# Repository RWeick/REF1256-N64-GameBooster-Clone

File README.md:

# REF1256-N64-GameBooster-Clone
An open source clone of the Datel GameBooster for the Nintendo 64

This is a fully functional Nintendo 64 GameBooster clone. It implements the original LZ9FC17 GAL on an Altera EPM570, and fully supports all functionality to include: loading Gameboy cartridges and the GS button.

This is compatible with the Sanni Cartridge Reader's N64 Gameshark programming function.

The 2x5 10 pin connector is mapped to the standard Altera USB Blaster pinout for programming. Happy making.

PCB Thickness: 1.2 mm

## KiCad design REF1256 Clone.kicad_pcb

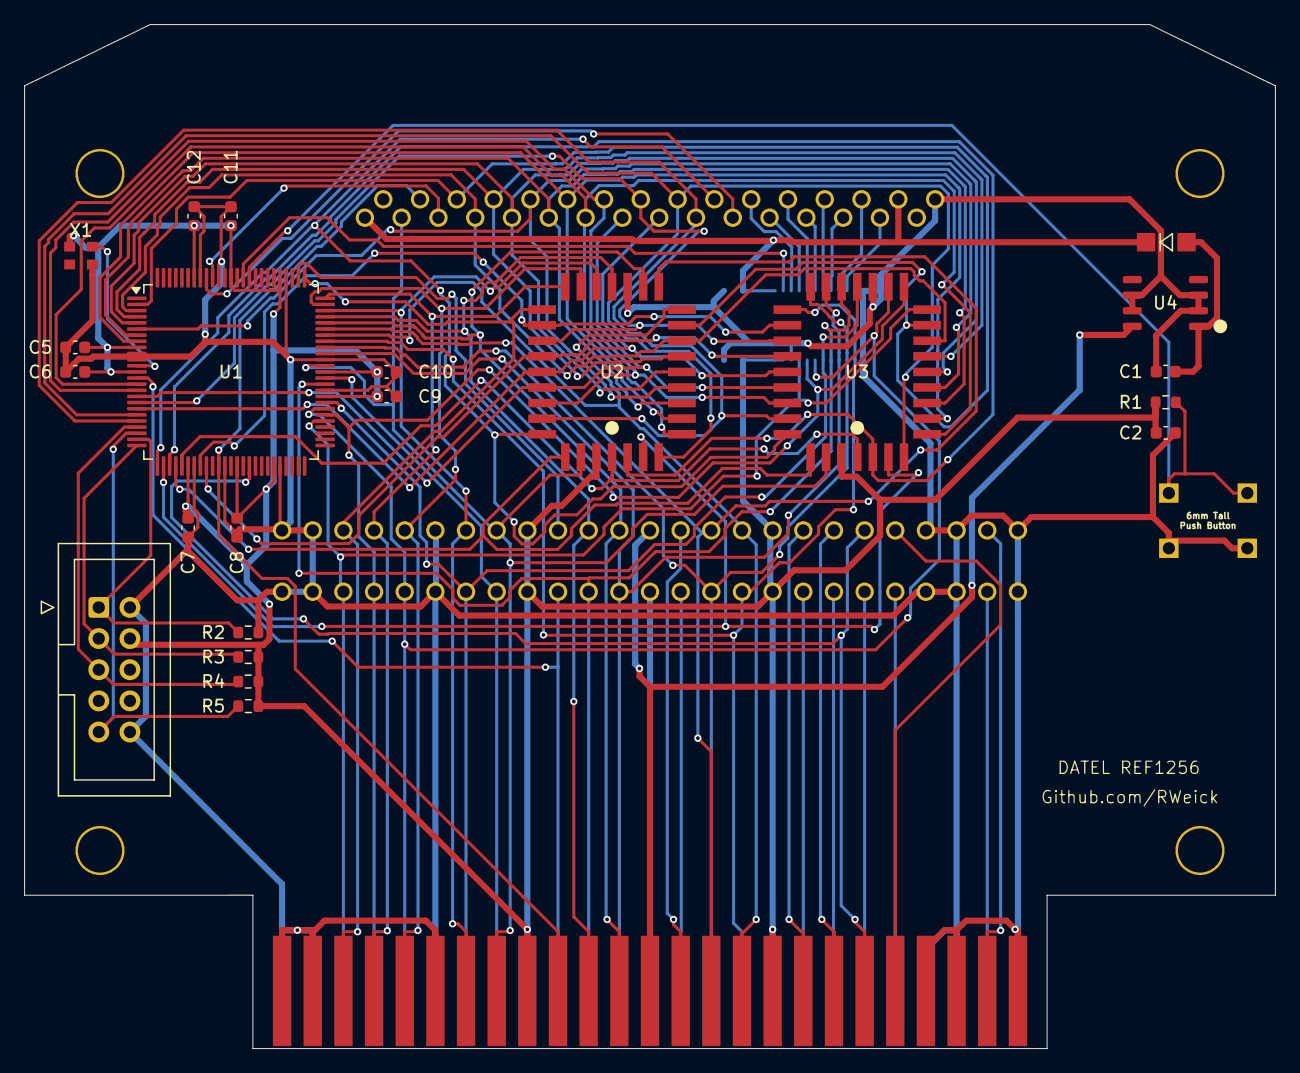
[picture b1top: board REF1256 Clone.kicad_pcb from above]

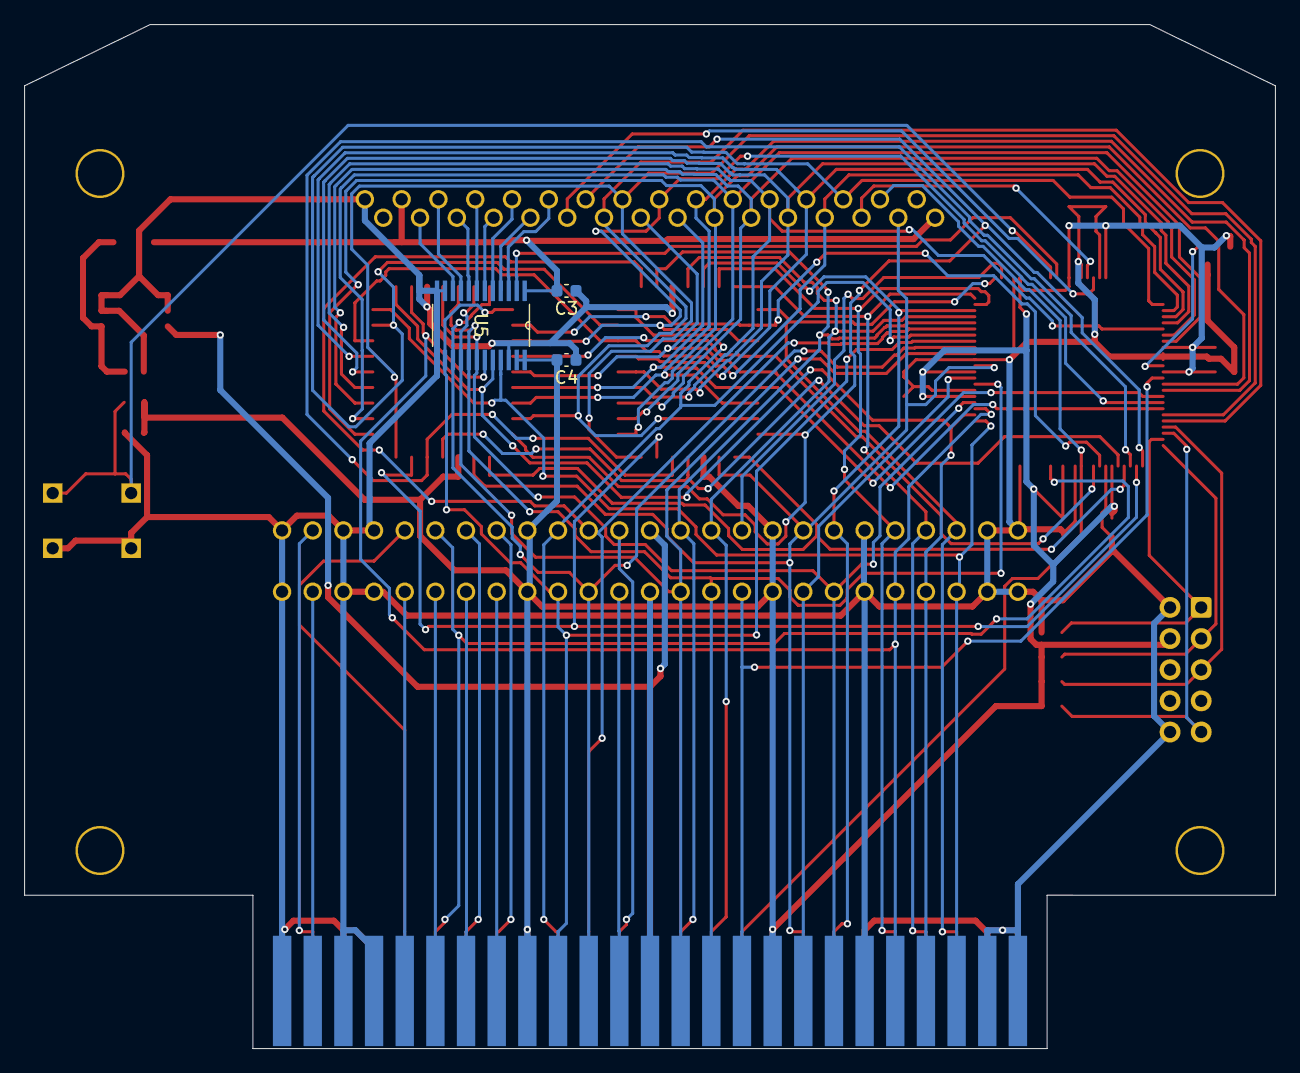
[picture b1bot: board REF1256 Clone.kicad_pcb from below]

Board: 2 copper layers, 102.0 x 83.5 mm, 30 parts (3 on the bottom side), 77 nets.

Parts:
C1, C2, C5, C6, C7, C8, C9, C10, C11, C12: 100 nF; C_0603_1608Metric
C3, C4: 100n; C_0603_1608Metric
D1: D_Small; Diode
Holes: Drill Holes
J1: Gameboy Cartridge Connector; Gameboy Slot
J2: N64 Cartridge Slot; Cartridge Slot
J3: Edge_Connector; Bottom Edge Connector
J4: Conn_02x05_Odd_Even; IDC-Header_2x05_P2.54mm_Vertical
R1, R2, R3, R4, R5: 10K Ohm; R_0603_1608Metric
SW1: SW_Push; 6mm Push Button
U1: EPM570T100; LQFP-100_14x14mm_P0.5mm
U2, U3: SST28LF040; PLCC32
U4: LM78L05_SO8; LM7805
U5: SN74LVC4245A
X1: ASCO; 50 MHz Crystal

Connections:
+3V3: C2.1, C4.2, C5.2, C6.2, C7.2, C8.2, C9.1, C10.1, C11.1, C12.1, J2.9 (3.3V), J2.17 (3.3V), J2.34 (3.3V), J2.42 (3.3V), J3.9 (3.3V), J3.17 (3.3V), J3.34 (3.3V), J3.42 (3.3V), J4.4, R1.1, R3.2, R4.2, R5.2, U1.9 (VCCIO1), U1.13 (VCCINT), U1.31 (VCCIO1), U1.39 (VCCINT), U1.45 (VCCIO1), U1.59 (VCCIO2), U1.63 (VCCINT), U1.80 (VCCIO2), U1.88 (VCCINT), U1.94 (VCCIO2), U2.32 (VCC), U3.32 (VCC), U5.23 (VCCB), U5.24 (VCCB), X1.4 (VDD)
/5V.VCC: C3.2, D1.1 (K), J1.1 (+5V), J1.30 (Reset), U5.1 (VCCA)
/5V.VOUT: C1.2, D1.2 (A), U4.1 (OUT)
/12V_Front: J2.13 (12V), J3.13 (12V), U4.8 (IN)
/12V_Rear: J2.38 (12V), J3.38 (12V)
/A0: J1.6 (A0), U1.2 (IO1_2), U2.12 (A0), U3.12 (A0)
/A1: J1.7 (A1), U1.3 (IO1_3), U2.11 (A1), U3.11 (A1)
/A2: J1.8 (A2), U1.4 (IO1_4), U2.10 (A2), U3.10 (A2)
/A3: J1.9 (A3), U1.5 (IO1_5), U2.9 (A3), U3.9 (A3)
/A4: J1.10 (A4), U1.6 (IO1_6), U2.8 (A4), U3.8 (A4)
/A5: J1.11 (A5), U1.7 (IO1_7), U2.7 (A5), U3.7 (A5)
/A6: J1.12 (A6), U1.8 (IO1_8), U2.6 (A6), U3.6 (A6)
/A7: J1.13 (A7), U1.15 (IO1_15), U2.5 (A7), U3.5 (A7)
/A8: J1.14 (A8), U1.16 (IO1_16), U2.27 (A8), U3.27 (A8)
/A9: J1.15 (A9), U1.17 (IO1_17), U2.26 (A9), U3.26 (A9)
/A10: J1.16 (A10), U1.18 (IO1_18), U2.23 (A10), U3.23 (A10)
/A11: J1.17 (A11), U1.19 (IO1_19), U2.25 (A11), U3.25 (A11)
/A12: J1.18 (A12), U1.20 (IO1_20), U2.4 (A12), U3.4 (A12)
/A13: J1.19 (A13), U1.21 (IO1_21), U2.28 (A13), U3.28 (A13)
/A14: J1.20 (A14), U1.26 (IO1_26), U2.29 (A14), U3.29 (A14)
/A15: U1.27 (IO1_27), U2.3 (A15), U3.3 (A15)
/A16: U1.28 (IO1_28), U2.2 (A16), U3.2 (A16)
/A17: U1.29 (IO1_29), U2.30 (A17), U3.30 (A17)
/A18: U1.30 (IO1_30), U2.1 (A18), U3.1 (A18)
/AD0: J2.28 (AD0), J3.28 (AD0), U1.55 (IO2_55), U3.13 (Ad8), U5.21 (B1)
/AD0.5V: J1.22 (Data_0), U5.3 (A1)
/AD1: J2.29 (AD1), J3.29 (AD1), U1.56 (IO2_56), U3.14 (Ad9), U5.20 (B2)
/AD1.5V: J1.23 (Data_1), U5.4 (A2)
/AD2: J2.30 (AD2), J3.30 (AD2), U1.57 (IO2_57), U3.15 (Ad10), U5.19 (B3)
/AD2.5V: J1.24 (Data_2), U5.5 (A3)
/AD3: J2.32 (AD3), J3.32 (AD3), U1.58 (IO2_58), U3.17 (Ad11), U5.18 (B4)
/AD3.5V: J1.25 (Data_3), U5.6 (A4)
/AD4: J2.36 (AD4), J3.36 (AD4), U1.61 (IO2_61), U3.18 (Ad12), U5.17 (B5)
/AD4.5V: J1.26 (Data_4), U5.7 (A5)
/AD5: J2.37 (AD5), J3.37 (AD5), U1.66 (IO2_66), U3.19 (Ad13), U5.16 (B6)
/AD5.5V: J1.27 (Data_5), U5.8 (A6)
/AD6: J2.40 (AD6), J3.40 (AD6), U1.67 (IO2_67), U3.20 (Ad14), U5.15 (B7)
/AD6.5V: J1.28 (Data_6), U5.9 (A7)
/AD7: J2.41 (AD7), J3.41 (AD7), U1.68 (IO2_68), U3.21 (Ad15), U5.14 (B8)
/AD7.5V: J1.29 (Data_7), U5.10 (A8)
/AD8: J2.16 (AD8), J3.16 (AD8), U1.69 (IO2_69), U2.13 (Ad0)
/AD9: J2.15 (AD9), J3.15 (AD9), U1.70 (IO2_70), U2.14 (Ad1)
/AD10: J2.12 (AD10), J3.12 (AD10), U1.71 (IO2_71), U2.15 (Ad2)
/AD11: J2.11 (AD11), J3.11 (AD11), U1.72 (IO2_72), U2.17 (Ad3)
/AD12: J2.7 (AD12), J3.7 (AD12), U1.73 (IO2_73), U2.18 (Ad4)
/AD13: J2.5 (AD13), J3.5 (AD13), U1.74 (IO2_74), U2.19 (Ad5)
/AD14: J2.4 (AD14), J3.4 (AD14), U1.75 (IO2_75), U2.20 (Ad6)
/AD15: J2.3 (AD15), J3.3 (AD15), U1.76 (IO2_76), U2.21 (Ad7)
/ALE_H: J2.35 (ALE_H), J3.35 (ALE_H), U1.14 (IO1_14/GCLK1)
/ALE_L: J2.33 (ALE_L), J3.33 (ALE_L), U1.62 (IO2_62/GCLK2)
/Button: R1.2, SW1.2, U1.85 (IO2_85)
/CIC.11: J2.19 (CIC_11), J3.19 (CIC_11)
/CIC.14: J2.43 (CIC_14), J3.43 (CIC_14)
/CIC.15: J2.18 (CIC_15), J3.18 (CIC_15)
/CLK: U1.12 (IO1_12/GCLK0), X1.3 (OUT)
/Chip_Enable: U1.33 (IO1_33), U2.22 (CE#), U3.22 (CE#)
/Gameboy.A15: J1.21 (A15), U1.92 (IO2_92)
/Gameboy.CS: J1.5 (CS), U1.91 (IO2_91)
/LAUDIO: J2.24 (LAUDIO), J3.24 (LAUDIO)
/Output_Enable: U1.34 (IO1_34), U2.24 (OE#), U3.24 (OE#)
/RAUDIO: J2.49 (RAUDIO), J3.49 (RAUDIO)
/S_DAT: J2.21 (EEPROM_DAT), J3.21 (EEPROM_DAT)
/Shift.Dir: U1.86 (IO2_86), U5.2 (DIR)
/TCK: J4.1, R2.1, U1.24 (TCK)
/TDI: J4.9, R5.1, U1.23 (TDI)
/TDO: J4.3, R3.1, U1.25 (TDO)
/TMS: J4.5, R4.1, U1.22 (TMS)
/UNUSED_Front: J2.14 (12V), J3.14 (12V)
/UNUSED_Rear: J2.39 (12V), J3.39 (12V)
/Video.Sync: J2.46 (VIDEO_SYNC), J3.46 (VIDEO_SYNC)
//COLD_RESET: J2.20 (/ColdReset), J3.20 (/ColdReset), U1.41 (IO1_41)
//INT1: J2.44 (/INT1), J3.44 (/INT1)
//NMI: J2.45 (/NMI), J3.45 (/NMI)
//read_bottom: J1.4 (Read), J3.10 (/RD), U1.36 (IO1_36)
//read_top: J2.10 (/RD), U1.77 (IO2_77)
//write: J1.3 (Write), J2.8 (/WR), J3.8 (/WR), U1.64 (IO2_64/GCLK3), U2.31 (WE#), U3.31 (WE#)
GND: C1.1, C2.2, C3.1, C4.1, C5.1, C6.1, C7.1, C8.1, C9.2, C10.2, C11.2, C12.2, J1.32 (GND), J2.1 (GND), J2.2 (GND), J2.6 (GND), J2.22 (GND), J2.23 (GND), J2.25 (GND), J2.26 (GND), J2.27 (GND), J2.31 (GND), J2.47 (GND), J2.48 (GND), J2.50 (GND), J3.1 (GND), J3.2 (GND), J3.6 (GND), J3.22 (GND), J3.23 (GND), J3.25 (GND), J3.26 (GND), J3.27 (GND), J3.31 (GND), J3.47 (GND), J3.48 (GND), J3.50 (GND), J4.2, J4.10, R2.2, SW1.1, U1.10 (GNDIO), U1.11 (GNDINT), U1.32 (GNDIO), U1.37 (GNDINT), U1.46 (GNDIO), U1.60 (GNDIO), U1.65 (GNDINT), U1.79 (GNDIO), U1.90 (GNDINT), U1.93 (GNDIO), U2.16 (GND), U3.16 (GND), U4.2 (GND), U4.3 (GND), U4.6 (GND), U4.7 (GND), U5.11 (GND), U5.12 (GND), U5.13 (GND), U5.22 (*OE), X1.2 (GND)
